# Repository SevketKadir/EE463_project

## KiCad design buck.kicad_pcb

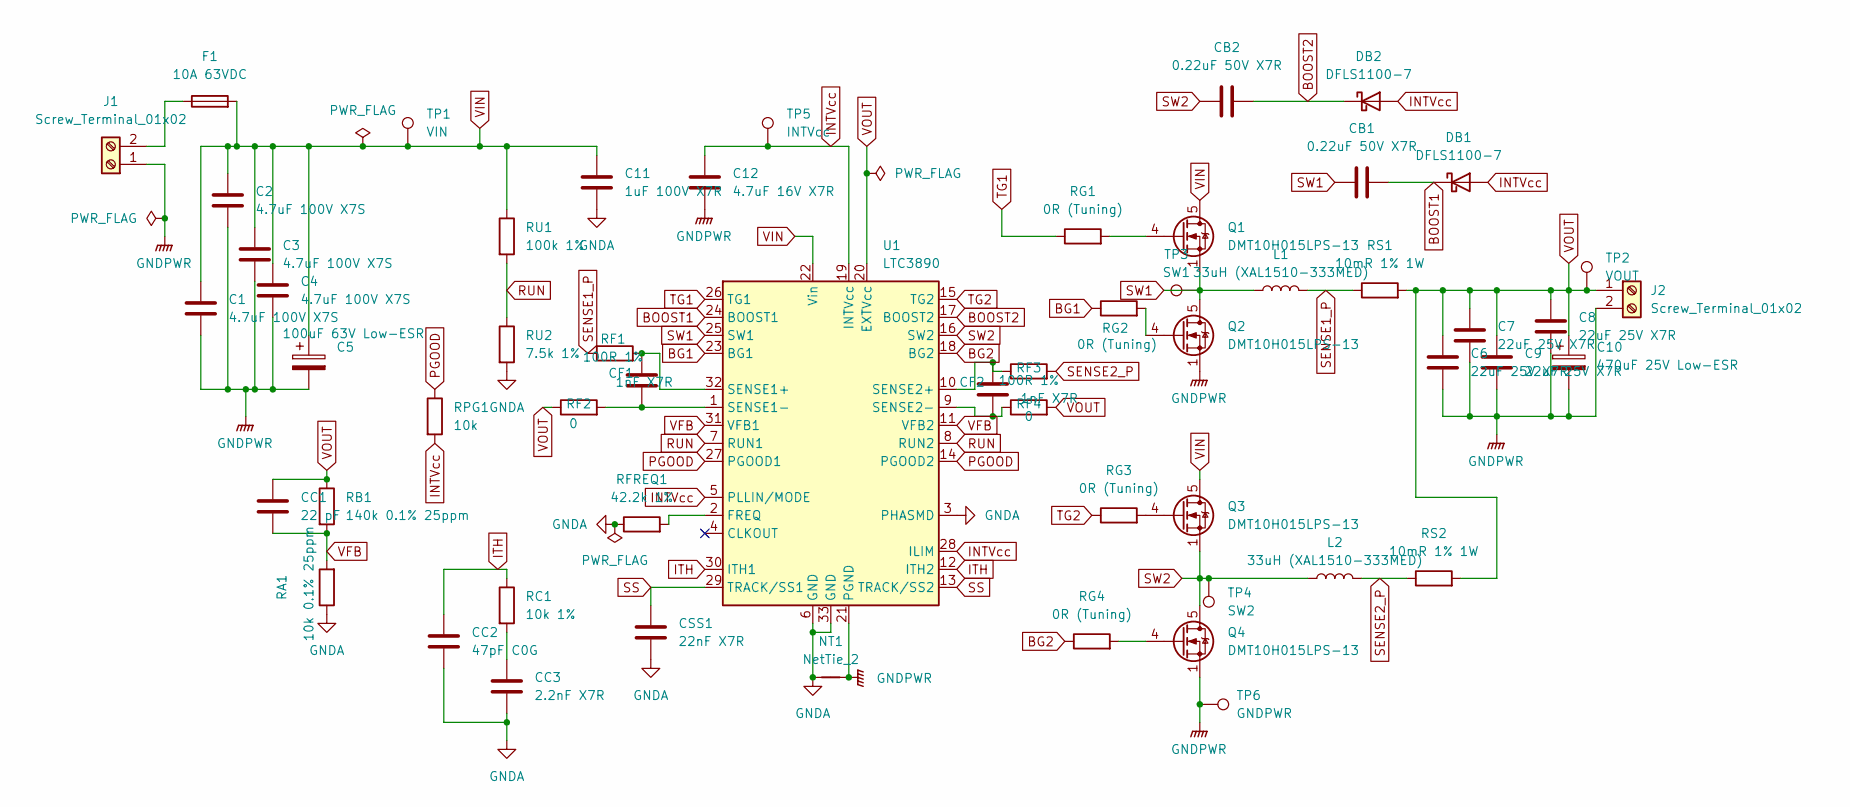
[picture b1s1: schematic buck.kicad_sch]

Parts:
C1, C2, C3, C4: 4.7uF 100V X7S; C_1210_3225Metric
C5: 100uF 63V Low-ESR; CP_Radial_D10.0mm_P5.00mm
C6, C7, C8, C9: 22uF 25V X7R; C_1210_3225Metric
C10: 470uF 25V Low-ESR; CP_Radial_D10.0mm_P5.00mm
C11: 1uF 100V X7R; C_1206_3216Metric
C12: 4.7uF 16V X7R; C_0805_2012Metric
CB1, CB2: 0.22uF 50V X7R; C_0603_1608Metric
CC1: 22 pF; C_0603_1608Metric
CC2: 47pF C0G; C_0603_1608Metric
CC3: 2.2nF X7R; C_0603_1608Metric
CF1, CF2: 1nF X7R; C_0603_1608Metric
CSS1: 22nF X7R; C_0603_1608Metric
DB1, DB2: DFLS1100-7; D_PowerDI-123
F1: 10A 63VDC; Fuseholder_Cylinder-5x20mm_Schurter_0031_8201_Horizontal_Op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
J1, J2: Screw_Terminal_01x02; TerminalBlock_Phoenix_MKDS-3-2-5.08_1x02_P5.08mm_Horizontal
L1, L2: 33uH (XAL1510-333MED); IND_XAL1510-333MED
NT1: NetTie_2; NetTie-2_SMD_Pad0.5mm
Q1, Q2, Q3, Q4: DMT10H015LPS-13; PowerDI5060-8_DMT10H015LPS-13
RA1: 10k 0.1% 25ppm; R_0603_1608Metric
RB1: 140k 0.1% 25ppm; R_0603_1608Metric
RC1: 10k 1%; R_0603_1608Metric
RF1, RF3: 100R 1%; R_0603_1608Metric
RF2, RF4: 0; R_0603_1608Metric
RFREQ1: 42.2k 1%; R_0603_1608Metric
RG1, RG2, RG3, RG4: 0R (Tuning); R_0603_1608Metric
RPG1: 10k; R_0603_1608Metric
RS1, RS2: 10mR 1% 1W; R_2512_6332Metric
RU1: 100k 1%; R_0603_1608Metric
RU2: 7.5k 1%; R_0603_1608Metric
TP1: VIN; TestPoint_Loop_D2.50mm_Drill1.0mm
TP2: VOUT; TestPoint_Pad_D1.5mm
TP3: SW1; TestPoint_Loop_D2.50mm_Drill1.0mm
TP4: SW2; TestPoint_Loop_D2.50mm_Drill1.0mm
TP5: INTVcc; TestPoint_Loop_D2.50mm_Drill1.0mm
TP6: GNDPWR; TestPoint_Pad_D1.5mm
U1: LTC3890; QFN-32-1EP_5x5mm_P0.5mm_EP3.45x3.45mm

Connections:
BG1: RG2.1, U1.23 (BG1)
BG2: RG4.1, U1.18 (BG2)
BOOST1: CB1.1, DB1.1 (K), U1.24 (BOOST1)
BOOST2: CB2.1, DB2.1 (K), U1.17 (BOOST2)
GNDA: C11.2, CC2.2, CC3.2, CSS1.2, NT1.1, RA1.1, RFREQ1.1, RU2.2, U1.3 (PHASMD), U1.6 (GND), U1.33 (GND)
GNDPWR: C1.2, C2.2, C3.2, C4.2, C5.2, C6.2, C7.2, C8.2, C9.2, C10.2, C12.2, J1.1, J2.2, NT1.2, Q2.1 (S), Q2.2 (S), Q2.3 (S), Q4.1 (S), Q4.2 (S), Q4.3 (S), TP6.1 (1_1), U1.21 (PGND)
INTVcc: C12.1, DB1.2 (A), DB2.2 (A), RPG1.2, TP5.1 (1_1), U1.5 (PLLIN/MODE), U1.19 (INTVcc), U1.28 (ILIM)
ITH: CC2.1, RC1.1, U1.12 (ITH2), U1.30 (ITH1)
unnamed: CC3.1, RC1.2
unnamed: F1.1, J1.2
unnamed: Q1.4 (G), RG1.2
unnamed: Q2.4 (G), RG2.2
unnamed: Q3.4 (G), RG3.2
unnamed: Q4.4 (G), RG4.2
unnamed: RFREQ1.2, U1.2 (FREQ)
unnamed: CF1.2, RF1.2, U1.32 (SENSE1+)
unnamed: CF1.1, RF2.2, U1.1 (SENSE1-)
unnamed: CF2.2, RF3.1, U1.10 (SENSE2+)
unnamed: CF2.1, RF4.1, U1.9 (SENSE2-)
PGOOD: RPG1.1, U1.14 (PGOOD2), U1.27 (PGOOD1)
RUN: RU1.2, RU2.1, U1.7 (RUN1), U1.8 (RUN2)
SENSE1_P: L1.2, RF1.1, RS1.1
SENSE2_P: L2.2, RF3.2, RS2.1
SS: CSS1.1, U1.13 (TRACK/SS2), U1.29 (TRACK/SS1)
SW1: CB1.2, L1.1, Q1.1 (S), Q1.2 (S), Q1.3 (S), Q2.5 (D), TP3.1 (1_1), U1.25 (SW1)
SW2: CB2.2, L2.1, Q3.1 (S), Q3.2 (S), Q3.3 (S), Q4.5 (D), TP4.1 (1_1), U1.16 (SW2)
TG1: RG1.1, U1.26 (TG1)
TG2: RG3.1, U1.15 (TG2)
VFB: CC1.2, RA1.2, RB1.2, U1.11 (VFB2), U1.31 (VFB1)
VIN: C1.1, C2.1, C3.1, C4.1, C5.1, C11.1, F1.2, Q1.5 (D), Q3.5 (D), RU1.1, TP1.1 (1_1), U1.22 (Vin)
VOUT: C6.1, C7.1, C8.1, C9.1, C10.1, CC1.1, J2.1, RB1.1, RF2.1, RF4.2, RS1.2, RS2.2, TP2.1 (1_1), U1.20 (EXTVcc)

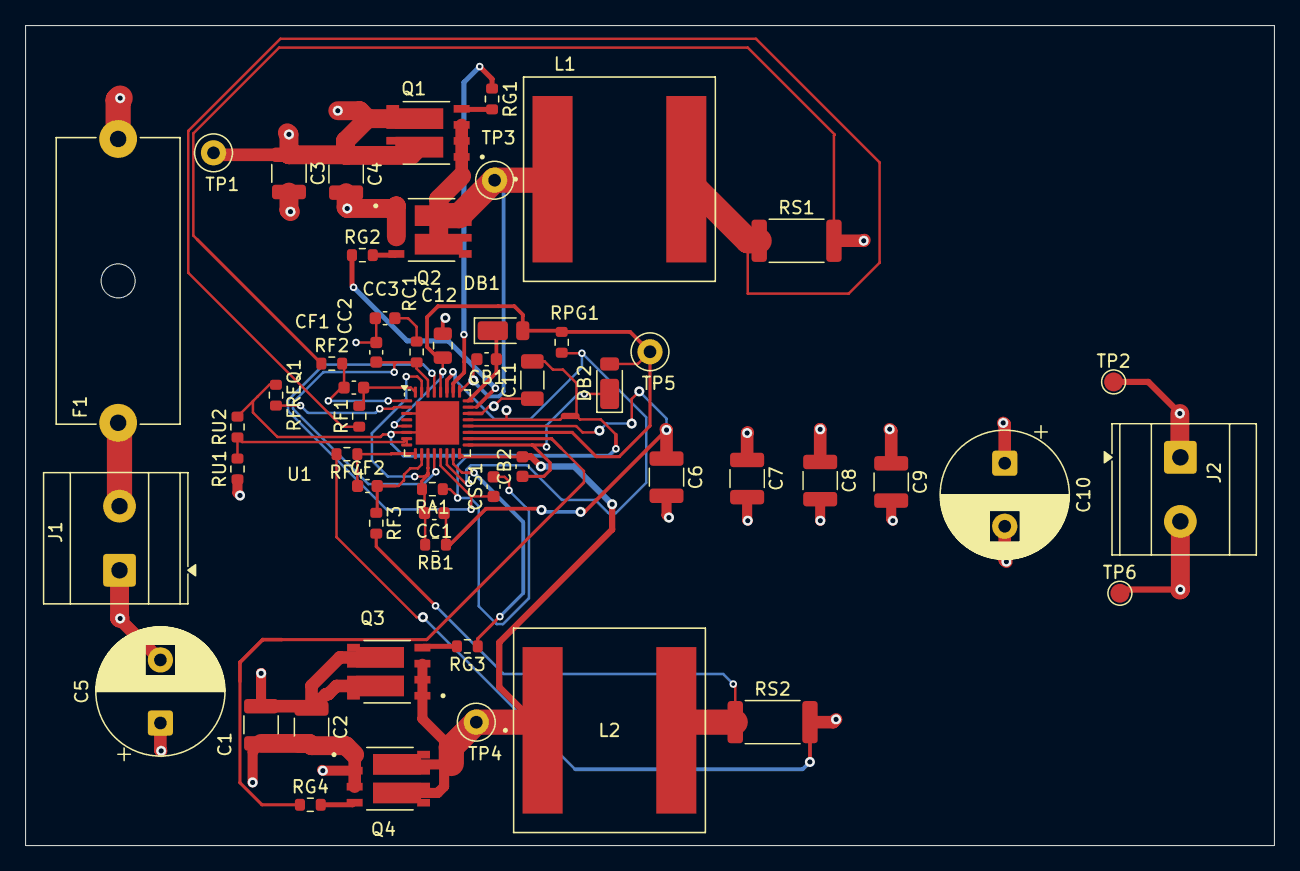
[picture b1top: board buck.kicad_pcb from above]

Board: 4 copper layers, 99.0 x 65.0 mm, 56 parts (0 on the bottom side), 31 nets.
